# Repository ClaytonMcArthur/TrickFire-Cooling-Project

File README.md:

# TrickFire Cooling System — Orin Fan Controller

A compact cooling controller for TrickFire Robotics. The project combines a custom **KiCad PCB**, an **Arduino Nano Every** for control, and an **I²C Python host** on an NVIDIA Jetson (**Orin/Nano**) to read temperature and drive multiple 5 V fans with PWM/low‑side switching.

---

## 📦 What’s in this repo

- `Trickfire Cooling System - Control PCB.kicad_sch` — Schematic (KiCad)
- `Trickfire Cooling System - Control PCB.kicad_pcb` — Board layout (KiCad)
- `ArduinoI2CComms.ino` — Arduino I²C firmware (slave device; fan control & telemetry)
- `TemperatureReader.ino` / `TemperatureReaderPWM.ino` / `Test1TempSensorTrickFire.ino` — Sensor/PWM test sketches
- `coolingI2C.py` — Host‑side Python tool to talk to the Arduino over I²C
- `PCB.png` — Render of the board
- `Schematic.png` — High‑level wiring diagram

> Note: The I²C address/command map live in `ArduinoI2CComms.ino` (kept generic here).

---

## 🛠️ Hardware overview

- **MCU**: Arduino **Nano Every**
- **Power**: 12 V input → 5 V buck (module shown: **LY‑KREE XS120503**)
- **Fan channels**: 4× low‑side NMOS drivers (e.g., **RFP30N06LE**) for 5 V brushless fans
- **Headers**: I²C (SCL/SDA), UART (RX1/TX1), additional GPIO
- **Stacks/planes**: solid GND pours, star power from buck to fans & MCU

### Connectors (silkscreen labels)
- **J11**: I²C **SCL/SDA**
- **J12**: **RX1/TX1** (UART to Orin / debug)
- **J5–J8**: Fan outputs (per‑channel NMOS)
- **J13**: Power entry / buck input (12 V)  
  *See schematic for exact pinouts.*

---

## 🔌 System architecture

1. **Jetson Orin/Nano** runs `coolingI2C.py` to send I²C commands (target setpoints / manual duty) and read temperatures/telemetry.
2. **Arduino Nano Every** (I²C slave) interprets commands and outputs PWM to the MOSFET gates for each fan channel.
3. **Control PCB** provides power distribution and MOSFET low‑side switching for the 5 V fans.

PCB:

Schematic:

---

## 🚀 Getting started

### 1) Hardware
- Feed **12 V** into the buck module; verify **5 V** at the fan rail and MCU.
- Connect fans to **J5–J8** (observe polarity). Keep total current within buck/MOSFET limits.
- Connect Orin/Nano I²C to **J11** (SCL/SDA) and common **GND**; optional UART via **J12**.

### 2) Firmware (Arduino)
- Open `ArduinoI2CComms.ino`, select **Arduino Nano Every**, and upload.
- Confirm the I²C address and any register/command IDs defined in the sketch.

### 3) Host (Python on Jetson)
```bash
sudo apt-get install -y python3-smbus i2c-tools
# Enable I²C in Jetson config if not already enabled
python3 coolingI2C.py -h   # view options/usage
```
- Typical flows:
  - **Manual**: set duty on one or more fan channels.
  - **Closed‑loop**: use `TemperatureReader*.ino` to read a sensor and map temperature → PWM.

---

## 🧪 Testing ideas
- Verify gate signals with a scope while sweeping duty.
- Spin up one channel at a time; monitor 5 V rail sag.
- Exercise thermal control by heating/cooling the sensor and watching duty track the setpoint.

---

## ⚠️ Safety & limits
- Size the buck regulator for **sum of fan currents + MCU margin**.
- Provide airflow and copper for MOSFET dissipation; keep traces short for gate loops.
- Add fusing on the 12 V input in the final build.

---

## 📁 Repo layout (suggested)
```
/firmware/        # Arduino sketches
/host/            # Python I²C tool + helpers
/hardware/        # KiCad files, images, exports
README.md
```

## 🙌 Acknowledgments
TrickFire Robotics contributors and reviewers.

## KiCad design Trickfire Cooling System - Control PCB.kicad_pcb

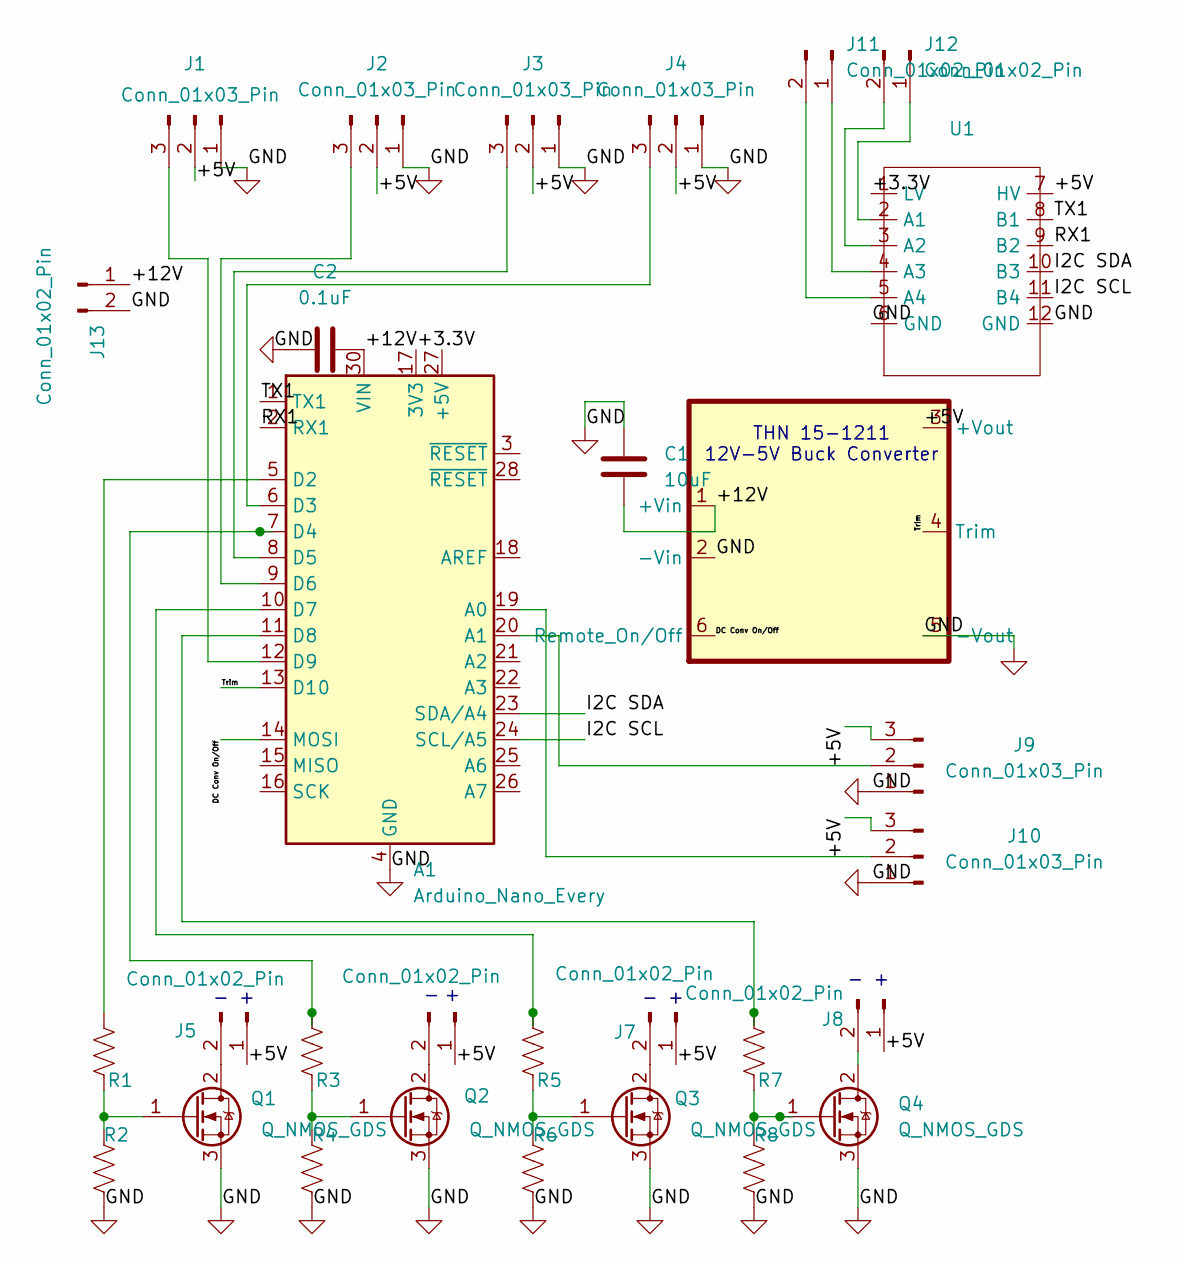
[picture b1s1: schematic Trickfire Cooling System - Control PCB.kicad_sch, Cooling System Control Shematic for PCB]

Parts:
A1: Arduino_Nano_Every; Arduino_Nano
C1: 10uF; 10uF electrolytic capacitor
C2: 0.1uF; CAPC2012X140N
J1, J2, J3, J4, J9, J10: Conn_01x03_Pin; JST_B3B-PH-K-S_LF__SN_
J5, J6, J7, J8, J11, J12: Conn_01x02_Pin; JST_B2B-PH-K-S
J13: Conn_01x02_Pin; CON2_1X2_P100
Q1, Q2, Q3, Q4: Q_NMOS_GDS; TRANS_RFP30N06LE
R1, R3, R5, R7: 39R; R_0805_2012Metric
R2, R4, R6, R8: 12k; R_0805_2012Metric
U1: Bi directional level changer 5 -3.3
U3: CONV_THN_15-1211

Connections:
/+3.3V: A1.17 (3V3), U1.1 (LV)
/+5V: J1.2, J2.2, J3.2, J4.2, J5.1, J6.1, J7.1, J8.1, J9.3, J10.3, U1.7 (HV), U3.3 (+Vout)
/+12V: A1.30 (VIN), C1.2, C2.2, J13.1, U3.1 (+Vin)
/DC Conv On/Off: A1.14 (MOSI), U3.6 (Remote_On/Off)
/I2C SCL: A1.24 (SCL/A5), U1.11 (B4)
/I2C SDA: A1.23 (SDA/A4), U1.10 (B3)
/RX1: A1.2 (RX1), U1.9 (B2)
/TX1: A1.1 (TX1), U1.8 (B1)
/Trim: A1.13 (D10), U3.4 (Trim)
GND: A1.4 (GND), A1.29 (GND), C1.1, C2.1, J1.1, J2.1, J3.1, J4.1, J9.1, J10.1, J13.2, Q1.3 (S), Q2.3 (S), Q3.3 (S), Q4.3 (S), R2.1, R4.1, R6.1, R8.1, U1.6 (GND), U1.12 (GND), U3.2 (-Vin), U3.5 (-Vout)
unnamed: A1.19 (A0), J10.2
unnamed: A1.20 (A1), J9.2
unnamed: A1.5 (D2), R1.1
unnamed: A1.6 (D3), J4.3
unnamed: A1.7 (D4), R3.1
unnamed: A1.8 (D5), J3.3
unnamed: A1.9 (D6), J2.3
unnamed: A1.10 (D7), R5.1
unnamed: A1.11 (D8), R7.1
unnamed: A1.12 (D9), J1.3
unnamed: J5.2, Q1.2 (D)
unnamed: J6.2, Q2.2 (D)
unnamed: J7.2, Q3.2 (D)
unnamed: J8.2, Q4.2 (D)
unnamed: J11.1, U1.4 (A3)
unnamed: J11.2, U1.5 (A4)
unnamed: J12.1, U1.2 (A1)
unnamed: J12.2, U1.3 (A2)
unnamed: Q1.1 (G), R1.2, R2.2
unnamed: Q2.1 (G), R3.2, R4.2
unnamed: Q3.1 (G), R5.2, R6.2
unnamed: Q4.1 (G), R7.2, R8.2

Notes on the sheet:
THN 15-1211 12V-5V Buck Converter

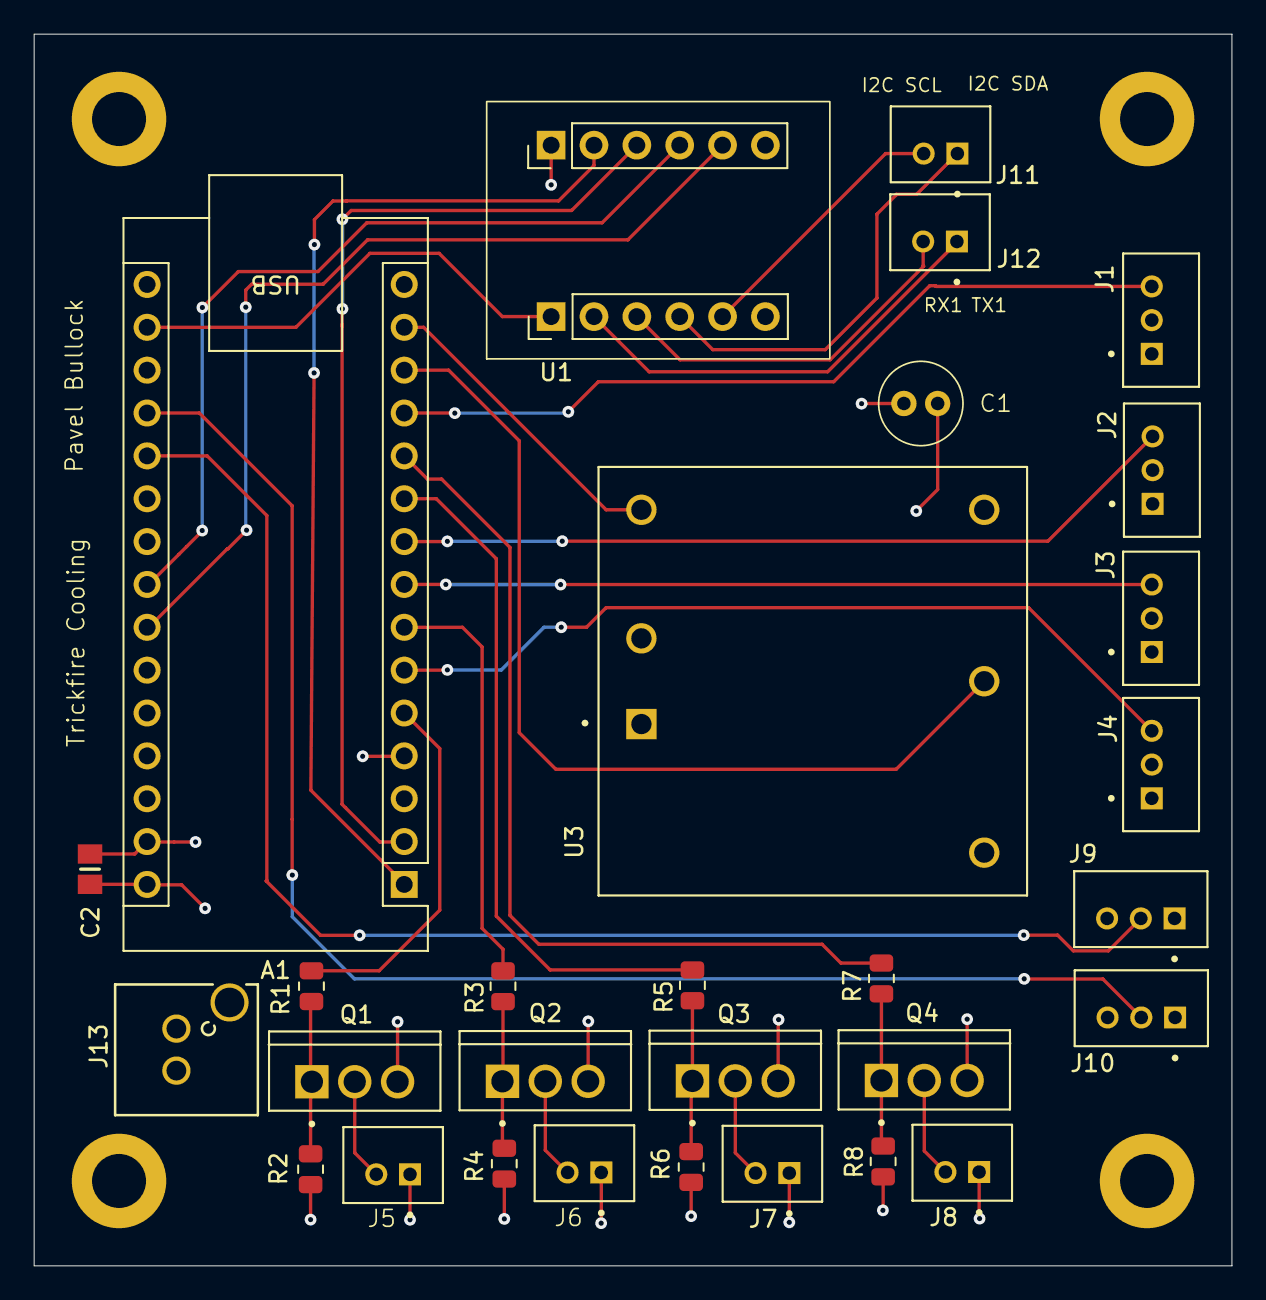
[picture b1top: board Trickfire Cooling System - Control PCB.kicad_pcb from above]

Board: 4 copper layers, 71.0 x 73.0 mm, 30 parts (0 on the bottom side), 32 nets.

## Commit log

2025-08-30 Rename README-3.md to README.md
